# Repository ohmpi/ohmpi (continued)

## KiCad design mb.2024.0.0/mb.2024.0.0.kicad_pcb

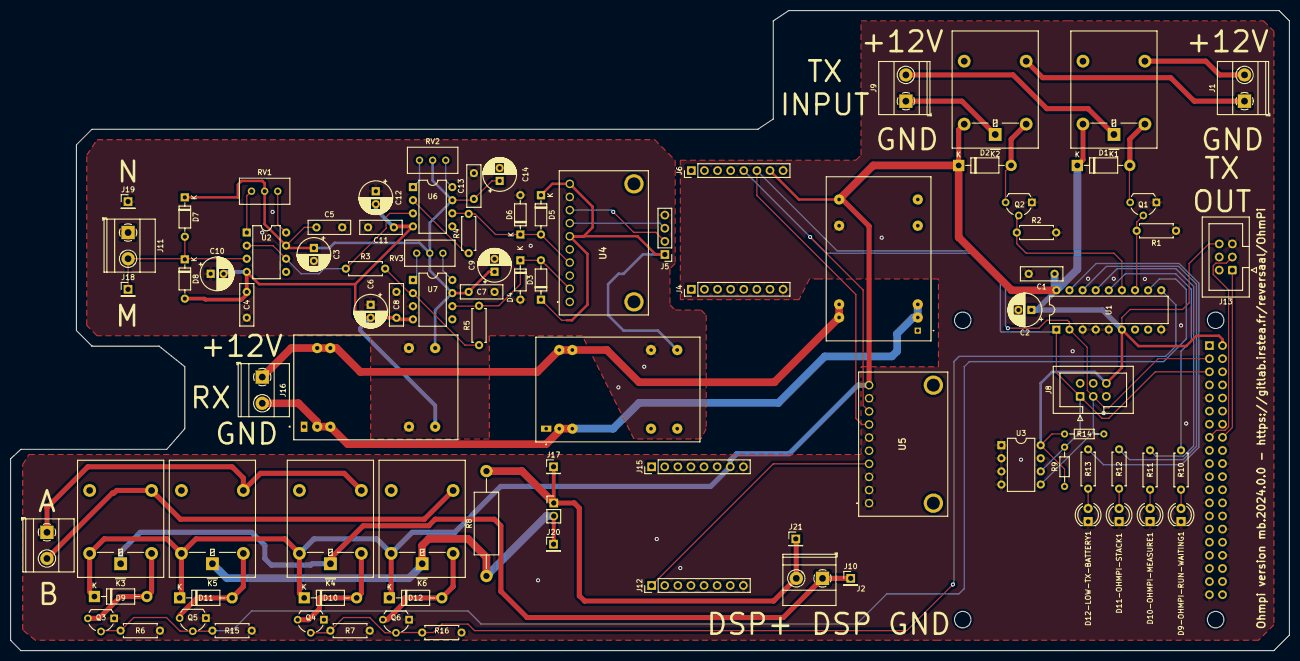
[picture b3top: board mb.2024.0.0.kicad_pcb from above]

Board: 2 copper layers, 247.8 x 124.0 mm, 92 parts (1 on the bottom side), 54 nets.

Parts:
Alim_5V_Digital_rasp_iso1540_mcp23008_current_7_click1, Alim_5V_I2C_isolator_Vmn_measurement1: THD_15-1211N; THD151211N
Alim_analog_Vmn_measurement_ina128P_lm158: THD_15-1222N; CONV_THD_15-1222N
C1, C4, C5, C7, C8, C11, C13: 100nF; C_Disc_D8.0mm_W2.5mm_P5.00mm
C2, C3, C6, C9, C10, C12, C14: 10uF; CP_Radial_D6.3mm_P2.50mm
D1, D2, D9, D10, D11, D12: 1N4001; D_DO-41_SOD81_P10.16mm_Horizontal
D3, D4, D5, D6, D7, D8: BAT86; D_DO-35_SOD27_P7.62mm_Horizontal
D9-OHMPI-RUN-WAITING1, D10-OHMPI-MEASURE1, D11-OHMPI-STACK1, D12-LOW-TX-BATTERY1: LED; LED_D4.0mm
J1: DSP_out_12v_GND; TerminalBlock_Phoenix_MKDS-1,5-2-5.08_1x02_P5.08mm_Horizont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
J2: DPS5005_input_0_to_50V; TerminalBlock_Phoenix_MKDS-1,5-2-5.08_1x02_P5.08mm_Horizont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
J3: Screw_Terminal_AB; TerminalBlock_Phoenix_MKDS-1,5-2-5.08_1x02_P5.08mm_Horizont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
J4, J6, J12, J15: Conn_01x08_Female; PinHeader_1x08_P2.54mm_Vertical
J5: Conn_01x04_Female; PinHeader_1x04_P2.54mm_Vertical
J7: Raspberry_Pi_2_3; PinSocket_2x20_P2.54mm_Vertical
J8: Connector_I2C_for_MCP23008; IDC-Header_2x03_P2.54mm_Vertical
J9: TX_bat; TerminalBlock_Phoenix_MKDS-1,5-2-5.08_1x02_P5.08mm_Horizont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
J10: DSP+; PinHeader_1x01_P2.54mm_Vertical
J11: Screw_Terminal_VMN; TerminalBlock_Phoenix_MKDS-1,5-2-5.08_1x02_P5.08mm_Horizont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
J13: Connector_I2C_for_mux; IDC-Header_2x03_P2.54mm_Vertical
J14: Conn_01x02_Female; PinHeader_1x02_P2.54mm_Vertical
J16: RX_bat; TerminalBlock_Phoenix_MKDS-1,5-2-5.08_1x02_P5.08mm_Horizont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
J17: DSP GND; PinHeader_1x01_P2.54mm_Vertical
J18: ELEC_M; PinHeader_1x01_P2.54mm_Vertical
J19: ELEC_N; PinHeader_1x01_P2.54mm_Vertical
J20: shunt +; PinHeader_1x01_P2.54mm_Vertical
J21: shunt -; PinHeader_1x01_P2.54mm_Vertical
K1, K2, K3, K4, K5, K6: G5LE-1; Relay_SPDT_Omron-G5LE-1
Q1, Q2, Q3, Q4, Q5, Q6: ZVN4206ASTZ; TO-92L_Wide
R1, R2, R6, R7, R15, R16: 100k; R_Axial_DIN0207_L6.3mm_D2.5mm_P7.62mm_Horizontal
R3, R4, R5: 1k; R_Axial_DIN0207_L6.3mm_D2.5mm_P7.62mm_Horizontal
R8: 2 ohms; R_Axial_DIN0414_L11.9mm_D4.5mm_P20.32mm_Horizontal
R9, R14: 4K7; R_Axial_DIN0204_L3.6mm_D1.6mm_P7.62mm_Horizontal
R10, R11, R12, R13: 330 ohms; R_Axial_DIN0207_L6.3mm_D2.5mm_P7.62mm_Horizontal
RV1, RV2, RV3: 10K; Potentiometer_Bourns_3296W_Vertical
U1: MCP23008-xP; DIP-18_W7.62mm
U2, U6, U7: OP07; DIP-8_W7.62mm
U3: 24LC02; DIP-8_W7.62mm
U4: 1115-Adress=0X49; 1085
U5: 1115-Adress=0X48; 1085

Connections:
5VA: Alim_5V_I2C_isolator_Vmn_measurement1.14 (+VOUT), D3.1 (K), D5.1 (K), J5.1, U4.6 (ADDR), U4.10 (VDD)
5VD: Alim_5V_Digital_rasp_iso1540_mcp23008_c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.14 (+VOUT), C1.1, C2.1, D1.1 (K), D2.1 (K), D9.1 (K), D10.1 (K), D11.1 (K), D12.1 (K), J6.7, J7.2 (5V), J8.6, J13.6, J15.7, K1.5, K2.5, K3.5, K4.5, K5.5, K6.5, R9.1, R14.1, U1.6 (~RESET), U1.18 (VDD), U3.8 (VCC), U5.10 (VDD)
+12V_A: Alim_analog_Vmn_measurement_ina128P_lm1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.14 (+VOUT), C3.1, C5.1, C7.1, C9.1, C13.1, C14.1, D7.1 (K), RV1.2, RV2.2, RV3.2, U2.7 (V+), U6.7 (V+), U7.7 (V+)
+12V_RX_bat: Alim_5V_Digital_rasp_iso1540_mcp23008_c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.22 (+VIN_(VCC)_1), Alim_5V_Digital_rasp_iso1540_mcp23008_c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.23 (+VIN_(VCC)_2), Alim_5V_I2C_isolator_Vmn_measurement1.22 (+VIN_(VCC)_1), Alim_5V_I2C_isolator_Vmn_measurement1.23 (+VIN_(VCC)_2), Alim_analog_Vmn_measurement_ina128P_lm1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.22 (+VIN(VCC)), Alim_analog_Vmn_measurement_ina128P_lm1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.23 (+VIN(VCC)), J16.1
+12V_TX_bat: J9.1, K2.1
-12V_A: Alim_analog_Vmn_measurement_ina128P_lm1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.11 (-VOUT), C4.1, C6.2, C8.1, C10.2, C11.1, C12.2, D8.2 (A), U2.4 (V-), U6.4 (V-), U7.4 (V-)
/Current_injection_and_measurement/A: J3.1, K4.3, K5.3
/Current_injection_and_measurement/B: J3.2, K3.3, K6.3
/Current_injection_and_measurement/Input_DSP_+_alim: J2.1, J10.1, K3.1, K4.1
/Current_injection_and_measurement/Input_DSP_GND_alim: J2.2, J14.1, J17.1, J21.1, R8.2
/Relay_switch_dsp/out_12v_DSP: J1.1, K2.3
/Relay_switch_dsp/out_GND_DSP: J1.2, K1.3
/Vmn_measurement/Electrode_M: D7.2 (A), D8.1 (K), J11.2, J18.1, U2.3 (+)
AN: J12.1, U5.4 (A0)
GNDA: Alim_5V_I2C_isolator_Vmn_measurement1.16 (-VOUT), Alim_analog_Vmn_measurement_ina128P_lm1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.9 (COMMON), Alim_analog_Vmn_measurement_ina128P_lm1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.16 (COMMON), C3.2, C4.2, C5.2, C6.1, C7.2, C8.2, C9.2, C10.1, C11.2, C12.1, C13.2, C14.2, D4.2 (A), D6.2 (A), J5.4, J11.1, J19.1, U4.9 (GND), U7.3 (+)
GNDD: Alim_5V_Digital_rasp_iso1540_mcp23008_c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.16 (-VOUT), C1.2, C2.2, D9-OHMPI-RUN-WAITING1.1 (K), D10-OHMPI-MEASURE1.1 (K), D11-OHMPI-STACK1.1 (K), D12-LOW-TX-BATTERY1.1 (K), J4.8, J6.8, J7.6 (GND), J7.9 (GND), J7.14 (GND), J7.20 (GND), J7.25 (GND), J7.30 (GND), J7.34 (GND), J7.39 (GND), J8.5, J12.8, J13.5, J15.8, Q1.1, Q2.1, Q3.1, Q4.1, Q5.1, Q6.1, R1.1, R2.2, R6.1, R7.1, R15.1, R16.1, U1.3 (A2), U1.4 (A1), U1.5 (A0), U1.9 (VSS), U3.1 (A0), U3.2 (A1), U3.3 (A2), U3.4 (GND), U3.7 (WP), U5.1 (A3), U5.2 (A2), U5.3 (A1), U5.6 (ADDR), U5.9 (GND)
GND_RX_bat: Alim_5V_Digital_rasp_iso1540_mcp23008_c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.2 (-VIN_(GND)_1), Alim_5V_Digital_rasp_iso1540_mcp23008_c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.3 (-VIN_(GND)_2), Alim_5V_I2C_isolator_Vmn_measurement1.2 (-VIN_(GND)_1), Alim_5V_I2C_isolator_Vmn_measurement1.3 (-VIN_(GND)_2), Alim_analog_Vmn_measurement_ina128P_lm1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.2 (-VIN(GND)), Alim_analog_Vmn_measurement_ina128P_lm1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.3 (-VIN(GND)), J16.2
GND_TX_bat: J9.2, K1.1
GP0: Q4.2, Q6.2, R7.2, R16.2, U1.10 (GP0)
GP1: Q3.2, Q5.2, R6.2, R15.2, U1.11 (GP1)
GP2: Q1.2, R1.2, U1.12 (GP2)
GP3: Q2.2, R2.1, U1.13 (GP3)
GP4: R10.1, U1.14 (GP4)
GP5: R11.1, U1.15 (GP5)
GP6: R12.1, U1.16 (GP6)
GP7: R13.1, U1.17 (GP7)
unnamed: D1.2 (A), K1.2, Q1.3
unnamed: D2.2 (A), K2.2, Q2.3
unnamed: D3.2 (A), D4.1 (K), R5.2, U4.2 (A2), U7.6
unnamed: D5.2 (A), D6.1 (K), R4.2, U4.4 (A0), U6.6
unnamed: D9-OHMPI-RUN-WAITING1.2 (A), R10.2
unnamed: D9.2 (A), K3.2, Q3.3
unnamed: D10-OHMPI-MEASURE1.2 (A), R11.2
unnamed: D10.2 (A), K4.2, Q4.3
unnamed: D11-OHMPI-STACK1.2 (A), R12.2
unnamed: D11.2 (A), K5.2, Q5.3
unnamed: D12-LOW-TX-BATTERY1.2 (A), R13.2
unnamed: D12.2 (A), K6.2, Q6.3
unnamed: J14.2, J20.1, K5.1, K6.1, R8.1
unnamed: R3.1, U2.2 (-), U2.6, U6.3 (+)
unnamed: R3.2, R5.1, U7.2 (-)
unnamed: R4.1, U6.2 (-)
unnamed: RV1.1, U2.8 (VOS)
unnamed: RV1.3, U2.1 (VOS)
unnamed: RV2.1, U6.8 (VOS)
unnamed: RV2.3, U6.1 (VOS)
unnamed: RV3.1, U7.8 (VOS)
unnamed: RV3.3, U7.1 (VOS)
SCL1: J6.5, J7.5 (SCL/GPIO3), J8.1, R9.2, U1.1 (SCL), U3.6 (SCL), U5.8 (SCL)
SCL2: J5.2, U4.8 (SCL)
SCL3: J7.16 (GPIO23), J13.1
SDA1: J6.6, J7.3 (SDA/GPIO2), J8.3, R14.2, U1.2 (SDA), U3.5 (SDA), U5.7 (SDA)
SDA2: J5.3, U4.7 (SDA)
SDA3: J7.15 (GPIO22), J13.3

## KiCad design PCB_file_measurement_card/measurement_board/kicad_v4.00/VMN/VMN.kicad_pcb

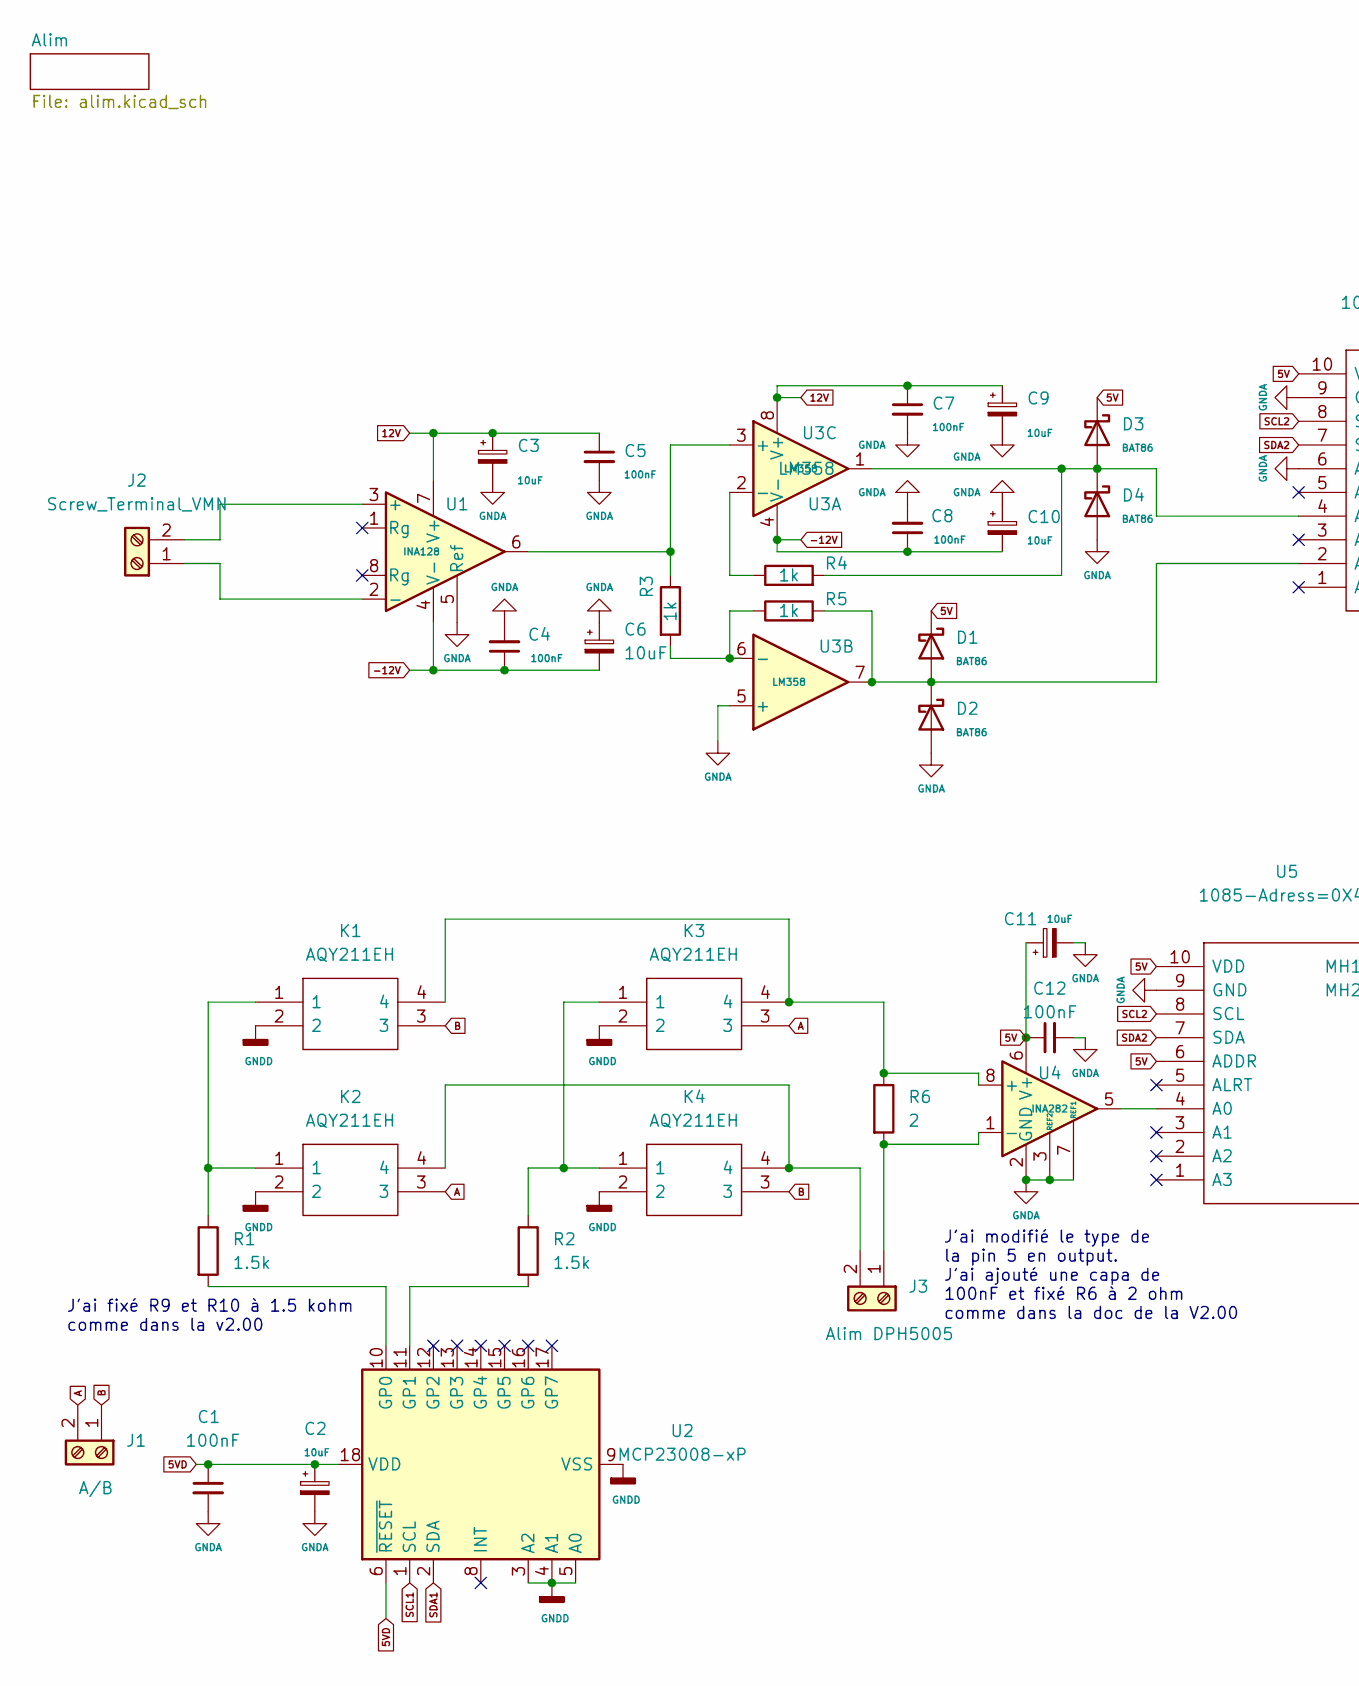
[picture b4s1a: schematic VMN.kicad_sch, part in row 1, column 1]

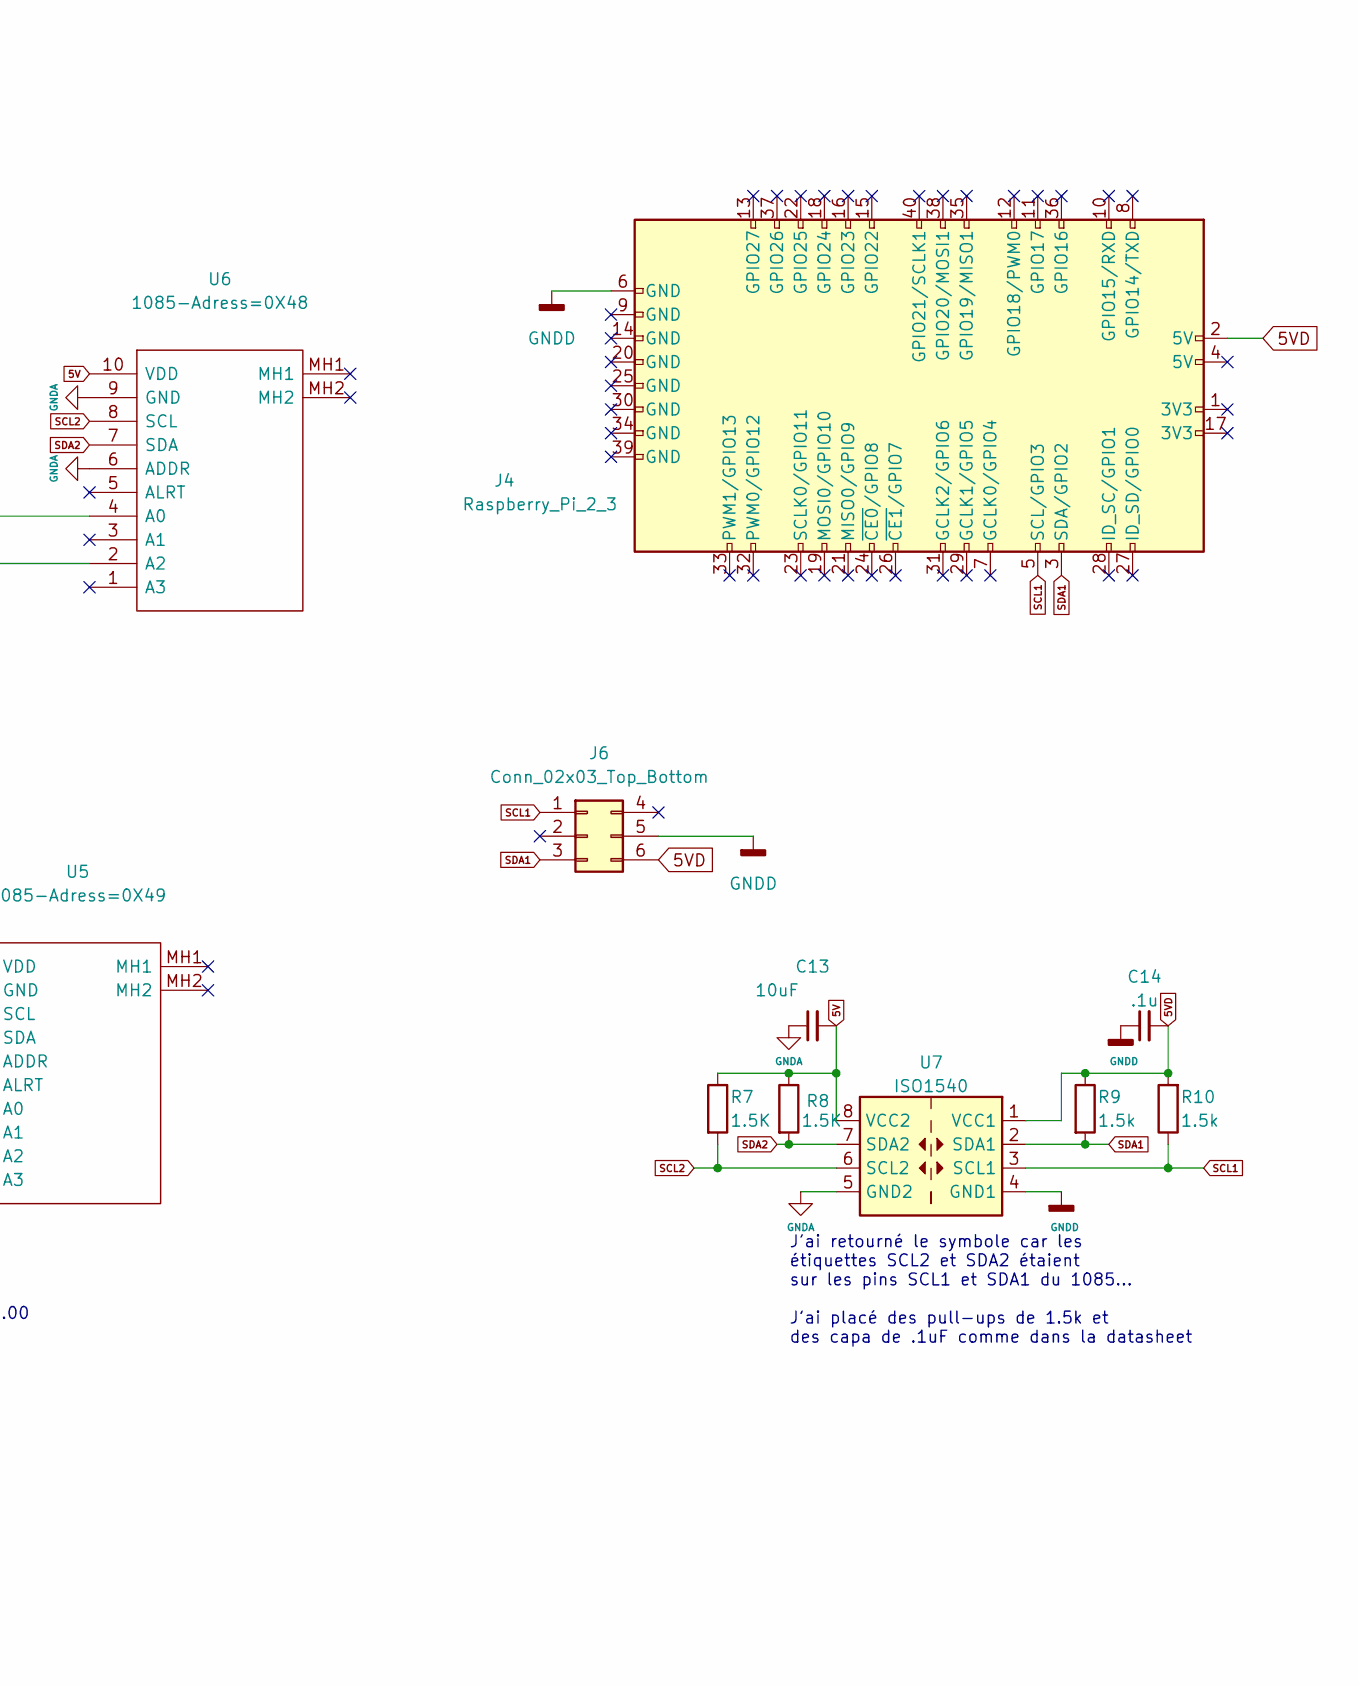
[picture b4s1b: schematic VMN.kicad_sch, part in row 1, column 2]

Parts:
C1, C4, C5, C7, C8, C12: 100nF; C_Disc_D8.0mm_W2.5mm_P5.00mm
C2, C3, C6, C9, C10, C11, C13: 10uF; CP_Radial_D6.3mm_P2.50mm
C14: .1u; C_Disc_D8.0mm_W2.5mm_P5.00mm
D1, D2, D3, D4: BAT86; D_DO-35_SOD27_P7.62mm_Horizontal
J1: A/B; TerminalBlock_Phoenix_MKDS-1,5-2-5.08_1x02_P5.08mm_Horizont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
J2: Screw_Terminal_VMN; TerminalBlock_Phoenix_MKDS-1,5-2-5.08_1x02_P5.08mm_Horizont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
J3: Alim DPH5005; TerminalBlock_Phoenix_MKDS-1,5-2-5.08_1x02_P5.08mm_Horizont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
J4: Raspberry_Pi_2_3; PinSocket_2x20_P2.54mm_Vertical
J6: Conn_02x03_Top_Bottom; IDC-Header_2x03_P2.54mm_Vertical
K1, K2, K3, K4: AQY211EH; DIP762W47P254L478H340Q4N; Manufacturer_Part_Number AQY211EH; Mouser Part Number 769-AQY211EH
R1, R2, R9, R10: 1.5k; R_Axial_DIN0207_L6.3mm_D2.5mm_P7.62mm_Horizontal
R3, R4, R5: 1k; R_Axial_DIN0207_L6.3mm_D2.5mm_P7.62mm_Horizontal
R6: 2; R_Axial_DIN0414_L11.9mm_D4.5mm_P20.32mm_Horizontal
R7, R8: 1.5K; R_Axial_DIN0207_L6.3mm_D2.5mm_P7.62mm_Horizontal
U1: INA128; DIP-8_W7.62mm
U2: MCP23008-xP; DIP-18_W7.62mm
U3: LM358; DIP-8_W7.62mm
U4: INA282; SOIC-8_3.9x4.9mm_P1.27mm
U5: 1085-Adress=0X49; 1085; PARTREV N/A; Mouser Part Number 485-1085
U6: 1085-Adress=0X48; 1085; PARTREV N/A; Mouser Part Number 485-1085
U7: ISO1540; SOIC-8_3.9x4.9mm_P1.27mm

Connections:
5V: C11.1, C12.1, C13.2, D1.1 (K), D3.1 (K), R7.1, R8.1, U4.6 (V+), U5.6 (ADDR), U5.10 (VDD), U6.10 (VDD), U7.8 (VCC2); also elsewhere on the board
5VD: C1.1, C2.1, C14.2, J4.2 (5V), J6.6, R9.1, R10.2, U2.6 (~RESET), U2.18 (VDD), U7.1 (VCC1); also elsewhere on the board
12V: C3.1, C5.1, C7.1, C9.1, U1.7 (V+), U3.8 (V+); also elsewhere on the board
-12V: C4.1, C6.2, C8.1, C10.2, U1.4 (V-), U3.4 (V-); also elsewhere on the board
A: J1.2, K2.3, K3.3
B: J1.1, K1.3, K4.3
GNDA: C1.2, C2.2, C3.2, C4.2, C5.2, C6.1, C7.2, C8.2, C9.2, C10.1, C11.2, C12.2, C13.1, D2.2 (A), D4.2 (A), U1.5 (Ref), U3.5 (+), U4.2 (GND), U4.3 (REF2), U4.7 (REF1), U5.9 (GND), U6.6 (ADDR), U6.9 (GND), U7.5 (GND2); also elsewhere on the board
GNDD: C14.1, J4.6 (GND), J6.5, K1.2, K2.2, K3.2, K4.2, U2.3 (A2), U2.4 (A1), U2.5 (A0), U2.9 (VSS), U7.4 (GND1); also elsewhere on the board
unnamed: D1.2 (A), D2.1 (K), R5.2, U3.7, U6.2 (A2)
unnamed: D3.2 (A), D4.1 (K), R4.2, U3.1, U6.4 (A0)
unnamed: J2.1, U1.2 (-)
unnamed: J2.2, U1.3 (+)
unnamed: J3.1, R6.2, U4.1 (-)
unnamed: J3.2, K2.4, K4.4
unnamed: K1.1, K2.1, R1.1
unnamed: K1.4, K3.4, R6.1, U4.8 (+)
unnamed: K3.1, K4.1, R2.1
unnamed: R1.2, U2.10 (GP0)
unnamed: R2.2, U2.11 (GP1)
unnamed: R3.1, U1.6, U3.3 (+)
unnamed: R3.2, R5.1, U3.6 (-)
unnamed: R4.1, U3.2 (-)
unnamed: U4.5, U5.4 (A0)
SCL1: J4.5 (SCL/GPIO3), J6.1, R10.1, U2.1 (SCL), U7.3 (SCL1)
SCL2: R7.2, U5.8 (SCL), U6.8 (SCL), U7.6 (SCL2)
SDA1: J4.3 (SDA/GPIO2), J6.3, R9.2, U2.2 (SDA), U7.2 (SDA1)
SDA2: R8.2, U5.7 (SDA), U6.7 (SDA), U7.7 (SDA2)

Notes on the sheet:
J'ai retourné le symbole car les étiquettes SCL2 et SDA2 étaient sur les pins SCL1 et SDA1 du 1085... J'ai placé des pull-ups de 1.5k et des capa de .1uF comme dans la datasheet
J'ai fixé R9 et R10 à 1.5 kohm comme dans la v2.00
J'ai modifié le type de la pin 5 en output. J'ai ajouté une capa de 100nF et fixé R6 à 2 ohm comme dans la doc de la V2.00

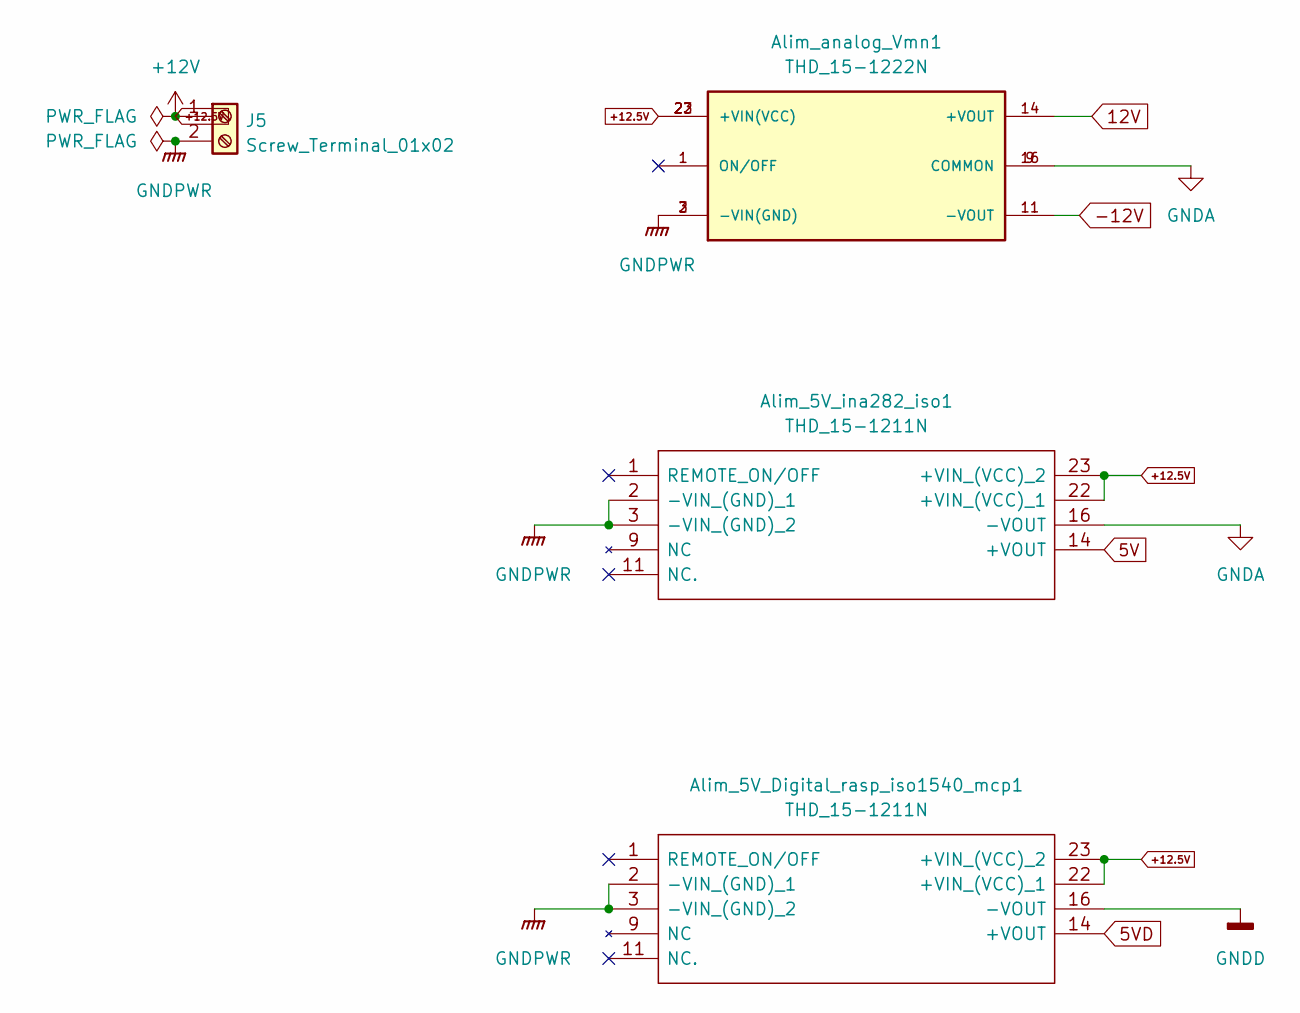
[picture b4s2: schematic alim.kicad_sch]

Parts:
Alim_5V_Digital_rasp_iso1540_mcp1, Alim_5V_ina282_iso1: THD_15-1211N; THD151211N; Manufacturer_Part_Number THD 15-1211N; Mouser Part Number 495-THD15-1211N
Alim_analog_Vmn1: THD_15-1222N; CONV_THD_15-1222N; PARTREV July 27, 2020
J5: Screw_Terminal_01x02; TerminalBlock_Phoenix_MKDS-1,5-2-5.08_1x02_P5.08mm_Horizont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

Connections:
5V: Alim_5V_ina282_iso1.14 (+VOUT); also elsewhere on the board
5VD: Alim_5V_Digital_rasp_iso1540_mcp1.14 (+VOUT); also elsewhere on the board
12V: Alim_analog_Vmn1.14 (+VOUT); also elsewhere on the board
+12.5V: Alim_5V_Digital_rasp_iso1540_mcp1.22 (+VIN_(VCC)_1), Alim_5V_Digital_rasp_iso1540_mcp1.23 (+VIN_(VCC)_2), Alim_5V_ina282_iso1.22 (+VIN_(VCC)_1), Alim_5V_ina282_iso1.23 (+VIN_(VCC)_2), Alim_analog_Vmn1.22 (+VIN(VCC)), Alim_analog_Vmn1.23 (+VIN(VCC)), J5.1
-12V: Alim_analog_Vmn1.11 (-VOUT); also elsewhere on the board
GNDA: Alim_5V_ina282_iso1.16 (-VOUT), Alim_analog_Vmn1.9 (COMMON), Alim_analog_Vmn1.16 (COMMON); also elsewhere on the board
GNDD: Alim_5V_Digital_rasp_iso1540_mcp1.16 (-VOUT); also elsewhere on the board
GNDPWR: Alim_5V_Digital_rasp_iso1540_mcp1.2 (-VIN_(GND)_1), Alim_5V_Digital_rasp_iso1540_mcp1.3 (-VIN_(GND)_2), Alim_5V_ina282_iso1.2 (-VIN_(GND)_1), Alim_5V_ina282_iso1.3 (-VIN_(GND)_2), Alim_analog_Vmn1.2 (-VIN(GND)), Alim_analog_Vmn1.3 (-VIN(GND)), J5.2

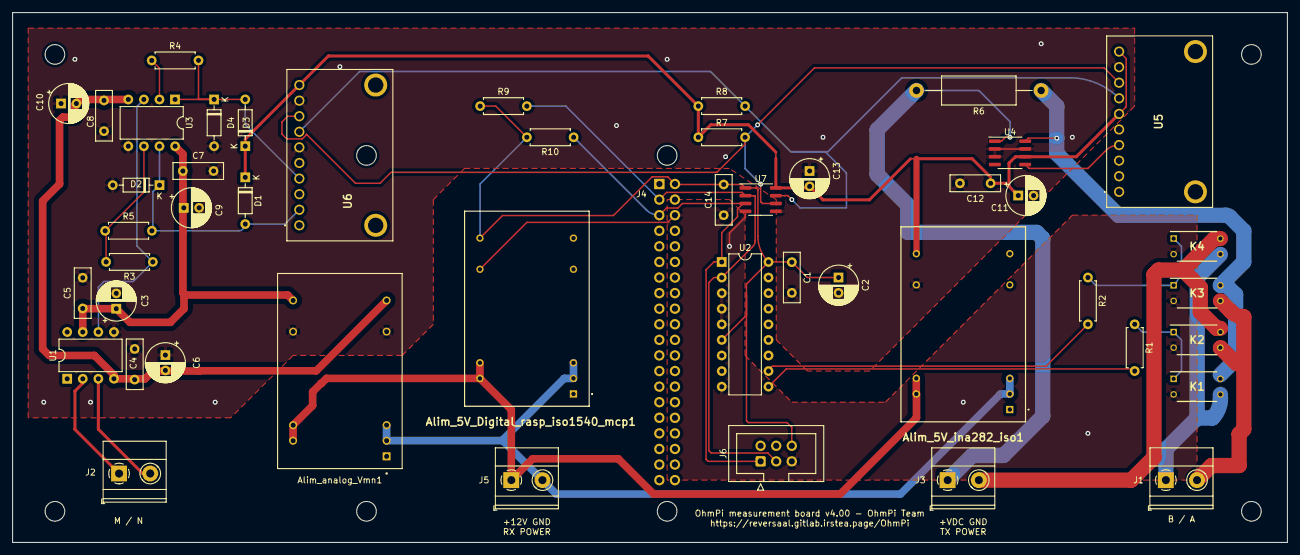
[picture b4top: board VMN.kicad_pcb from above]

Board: 2 copper layers, 207.8 x 86.4 mm, 48 parts (1 on the bottom side), 29 nets.

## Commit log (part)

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2024-06-28 Rename OhmPi to ohmpi in startup instructions for mqtt web interface
2024-06-28 #203 Uses the settings defined in config.py (was hardcoded before)
2024-06-30 Removes hex from soh_logger in MUX_2024_0_X init
2024-06-30 Adds colored text for soh_logger in MUX_2024_0_X init
2024-06-30 Adds colored text to identify mux board using soh_logger in MUX_2024_0_X init
2024-07-01 Adds minor changes to phmpi before merging v2024_0_bug_fix into 203_fix_issue
2024-07-01 Update BOM mux2024 and format
2024-07-01 Merges changes in pwr_dph5005
2024-07-01 fixes issue #212
2024-07-03 Use crontab to run web interface in user mode instead of rc.local, fix #195
2024-07-03 Fix #204
2024-07-03 v2024.0.15
2024-07-04 measurement board pads and track correction for THD
2024-07-04 update version number on the PCB
2024-07-04 Move sequence generator to sequence.py and refactor the code
2024-07-05 Fix typo in multigrad
2024-07-07 Import create_sequence()
2024-07-07 Add possible solution for #218 by asking the dph the UOUT in a breaking loop
2024-07-07 Update instruction for AP settings
2024-07-07 Update instruction ohmpiAP + fix bug data_web if data/ does not exists
2024-07-07 Add conversion from np.float64() to python float() when using numpy >= 2.0.0 This prevents logger reporting "Vmn": np.float64(3.22) instead of "Vmn": 3.22
2024-07-10 Fix typo
2024-07-10 Fix nonetype if no tca for mux2024
2024-07-10 v2024.0.16
2024-07-10 Fix issue with nonetype
2024-07-10 Update push_minor to fetch master before merging it (avoid conflicts)
2024-07-10 v2024.0.18
2024-07-10 Re-add back mux header on i2C test
2024-07-10 v2024.0.20
2024-07-10 If i2c_ext_tca not present, do not check for it
2024-07-10 v2024.0.22
2024-07-10 Web interface, don't overwrite log but append to it >> instead of >
2024-07-22 Modify figure to have width=100%, not fixed with, fix small doc typo
2024-07-22 Use figure instead of image within table (see #222)
2024-07-22 Improve for loop for setting DPH target voltage.
2024-07-22 Add config['pwr']['pwr_accuracy'] to control the for loop behavior of DPH5005
2024-07-22 Add quenched method (fix #133)
2024-07-22 v2024.0.25
2024-07-22 Polish OhmPi.create_sequence()
2024-07-22 Add joblib in requirements + fix fpath in OhmPi.create_sequence()
2024-07-23 Add OhmPi.set_time() in case RPI running in AP mode without internet
2024-07-23 Make joblib optional
2024-07-28 WIP accordion
2024-07-31 Add possibility to kill a multi-sequence acquisition during waiting time.
2024-08-07 Fix mux2024 pcb missing R10-gate ZVN connection
2024-08-07 Updates zone on MUX_2024.0.2 pcb
2024-08-10 Fix 'EVENT' error when setting up logger on new reinstantaion of OhmPi() WIP new UI, implement raw table
2024-08-11 Add log to webgui
2024-08-11 Add dpdp and wenner sequence
2024-08-11 Pass on sequence to sendCommand in saveConfigBtnFunc
2024-08-12 Add gradient and schlum array + download seq btn
2024-08-12 Add warning for soldering rpi header on under side of PCB + fix two -> three idc 6 pins
2024-08-13 Adding shortcut test for AB (working) and ABMN (not working great)
2024-08-13 WIP fixing webgui on the RPi
2024-08-19 Add ability to download files in a specified format in API
2024-08-19 Add invertedData retention + feedback inversion failed/success + fw avg info + download with specific ftype
2024-08-20 Update to user default mqtt_user and password (allow_anonymous=false)
2024-08-20 Update _test_mux_XX()
2024-08-20 Add everything ok
2024-08-20 Fix _test_mux_ABMN()
2024-08-20 Fix colored() and add np.median() for MN
2024-08-20 Fix swapped column in get_data()
2024-08-20 Update install.sh script for mqtt username/password default
2024-08-20 Fix traces quad when interrupted survey comes first
2024-08-20 Fix rscheck
2024-08-20 Update UI
2024-08-20 Update webgui
2024-08-20 Add V11 test (2.5V on A0 ADS voltage) to mb2025 checks
2024-08-21 v2024.0.26
2024-08-21 v2024.0.27
2024-09-18 Updates zone on MUX 2024 - no major change
2024-09-18 adds current_overload param and make it a setter getter to address #229
2024-09-18 fixes current_overload register to address #229
2024-09-18 Adds check to make current_overload not smaller than current_max #229
2024-09-23 Updates doc
2024-10-02 Update link to IDC socket and plug for mux2023
2024-10-07 Update relay mux2023 link with relay used in mux2024 (cheaper)
2024-10-07 Fix #232 (force countourpy version 1.0.1) as matplotlib dependency
2024-10-14 Fixes minor bug in mb_2024_1_X module
2024-10-19 Fixes bug documented in issue #236
2024-10-29 fix #237
2024-10-29 Update ohmpi.py export function
2024-10-30 Adds subclass management in rx init 2024_1_X
2024-10-30 Update dph_5005 specs
2024-10-30 Recompute pab_max
2024-10-30 v2024.0.28
2024-11-04 Remove os.chdir() from example
2024-11-04 WIP restructure
2024-11-04 Enforce numpy < 2.0.0 (fix float64 issues)
2024-11-04 Flatten software doc
2024-11-04 Add contributors section
2024-11-04 Reverts dph5005 voltage_max spec to 50.99V
2024-11-05 Adds a gain setting before each _find_vab
2024-11-05 Changes injection duration to 0.2s
2024-11-05 Add new directory
2024-11-05 Add new file
2024-11-05 Add hedges.rst
2024-11-05 add toctree
2024-11-05 Adds a message to debug
2024-11-05 Ajouter un nouveau répertoire
2024-11-05 Téléverser un nouveau fichier
2024-11-05 add pic hedges
2024-11-05 Update 2 files
    - /doc/source/source_rst/applications/hedges.rst
    - /doc/source/source_rst/gallery.rst
2024-11-05 add pic hedg
2024-11-05 Add slow ohmpi mqtt
2024-11-05 Changes iab_min
2024-11-05 Adds a debug message on iab_lower_bounds
2024-11-05 updates mux_2024_to_mux_2023
2024-11-05 Fix mapper in utils
2024-11-05 updates utils
2024-11-05 reset gain on tx before compute_vab
2024-11-05 fix reset gain on tx before compute_vab in mb_2023
2024-11-05 Set injection_duration in compute_vab
2024-11-05 Adds a short pulse of polarity 0 at the beginning of vab_square_wave
2024-11-05 Adds a short pulse of polarity 0 at the beginning of compute_vab
2024-11-05 ohmpi india first attempt at website
2024-11-05 Adapt example for 16 electrodes
2024-11-05 Update simple sequence example
2024-11-05 Fix dph5005 decay before setting vab in compute_vab
2024-11-05 Updates default.json and fixes small typos
2024-11-06 Reduce resolution size and remove old pictures
2024-11-06 add lab
2024-11-06 Remove unneeded pic
2024-11-06 Add map
2024-11-06 Update doc
2024-11-06 Update fig swale example
2024-11-06 Adds the interactive map module
2024-11-07 Add contributors
2024-11-07 Add marc
2024-11-07 coorection of example files
2024-11-07 Change pwr latency to 6s to be sure dph5005 is on
2024-11-07 v2024.0.33
2024-11-07 Remove source folder for doc
2024-11-07 Update ci with rules
2024-11-07 Small change
2024-11-07 Add map to system overview
2024-11-08 Update README.md with contributing section
2024-11-08 review how to contribute
2024-11-08 Add discord invitation link
2024-11-08 Add tips for a successfull ohmpi build
2024-11-08 Add pdf checklist for deployment
2024-11-08 Adding OhmPi.test() Tx.test() Rx.test()
2024-11-08 Add OhmPi.test_pwr()
2024-11-08 Fix tx.r_shunt() formula for deviation
2024-11-08 Add OhmPi.test() in troubleshooting
2024-11-08 Add CI test
2024-11-09 Improve coverage and add coverage.sh
2024-11-09 Add changelog
2024-11-09 Add posibility to write OhmPi.test(filename="test.json") to json (#259)
2024-11-09 Rename constant -> safe and full_constant -> fixed
2024-11-09 Add acquisition strategies in documentation
2024-11-10 Add documentation on pyramids of settings + graph of strategy (fix #211)
2024-11-10 Fix #196
2024-11-10 Implement injection_id
2024-11-10 Update UI with new headers and implement strategy
2024-11-10 Correct vmn_req unit from mV to V (also in webgui)
2024-11-10 Add calibration .py from hackathon 2024 (so we can remove calibration branch)
2024-11-11 Add new webgui pic + update description in doc + add video link
2024-11-11 Add hw_specs page
2024-11-11 Add 32bit os reason for slow ohmpi
2024-11-11 Add dg411 gain ratio (at rest! it works with mux) to OhmPi
2024-11-11 Fix #236
2024-11-11 Re-add pandas to requirements (for export, download, ...)
2024-11-11 Recommend restarting for reboot
2024-11-11 v2024.0.34
2024-11-11 Update bom list for mb2024
2024-11-13 Fixes typo and changes component link in MUX2024
2024-11-13 Adds link to boards in assemble systems
2024-11-14 Fix typo in troubleshooting
2024-11-26 Update pseudo-section screenshot webgui
2024-11-27 Tries to solve #267
2024-11-28 Fix doc bug with duplicated toctree in different pages (use links instead)
2024-11-28 Update to fix #267
2024-11-28 Add matplotlib to import
2024-11-29 Update mb2024 checks
2025-01-08 Add back gerber for mux2023.0.1 (fix #269)
2025-01-20 solves issue #271
2025-01-21 solves issue #271 by enlarging zones and removing via
2025-01-21 removing MUX.2024.0.2 #271
2025-01-22 adds new reference circuit #260
2025-01-29 Updates docs on MUX board v2024 after assembly
2025-01-29 Fixes I2C input on mux2024-text.jpg
2025-01-29 Fixes I2C input on mux2024-text.jpg and SCK in table
2025-02-05 adds error message when dph not connected via usb
2025-02-10 Updates doc on mux_2024
2025-02-11 Fix mb2024 test (no continuity with SDA/SCL from current click) + Add current debugging
2025-02-12 Add vmn voltage debugging instructions
2025-02-12 Add soldering to troubleshooting
2025-02-13 Restore __init__ line that dissapeared
2025-02-13 Fix dph5005 baudrate explanation
2025-02-13 Add warning for failed communication with power supply (inside ohmpihardware)
2025-02-13 Fix pseudo-section depth
2025-03-24 Add k.plot_last_fw() to troubleshooting
2025-03-28 updates checklist
2025-03-28 Add fw diagnostic to doc
2025-03-28 Add assembling of ohmpi lite 16
2025-03-28 Add ohmpi lite 16
2025-03-28 Add original pptx
2025-03-28 Fix number of mux
2025-03-28 updates strategy in example
2025-03-28 Enable shutdown, reboot and time set from user mode via os.system('sudo ...')
2025-03-28 Add 'sudo reboot' to reboot while in user mode
2025-03-29 Add mux bom list
2025-03-29 Supprimer ibom.html
2025-03-29 Update instructions for run_on_start
2025-03-29 Update bom in doc
2025-03-29 Add hardware error alert in webUI
2025-03-29 More general error mes
2025-03-29 Fixes issue 277
2025-03-29 v2024.0.35
2025-03-30 Typo specs 500 mA -> 50 mA
2025-03-30 updates doc ohmpi 16
2025-03-31 Update doc ok
2025-04-01 corrects manual check table for mux 2024
2025-04-01 Update order of mux2024 hardware check
2025-04-01 corrects manual check image for mux 2024
2025-04-01 Update doc mux2024-test
2025-04-01 Fix typo capa polarity step 15
2025-04-01 Add arrow step 15 on mb2024
2025-04-01 Update step15
2025-04-03 Add soh and ctrl to webgui
2025-04-03 Fix example from 'constant' to 'safe' in assembly doc
2025-04-03 Add numpy==1.26.4 to install_resipy.sh
2025-04-03 Update discord link
2025-04-03 Edit README.md
2025-04-03 Fix typo in geometric factor computation in UI
2025-04-04 Fix ohmpi_id read from config.py in webgui
2025-04-04 Fix #291
2025-04-06 Make more robust install.sh script
2025-04-07 removes sampling_interval references #202
2025-04-07 updates doc for mb2024
2025-04-07 updates doc for mux2024
2025-04-07 updates ohmpi map
2025-04-07 clarifies troubleshooting modbus
2025-04-07 clarifies troubleshooting intro
2025-04-07 Fix #289 and fix #282
2025-04-08 restructuring troubleshooting
2025-04-16 Update maps with latest registrations
2025-05-12 Fix typo + add discharge relay
2025-05-12 Add test mux2024 idc and screw
2025-08-25 Add .3f for electrodes
2025-08-26 Change fname_coord format to x,y,z csv with comma (like in ResIPy)
2025-09-08 Remove doc and add docs git submodule
2025-09-08 Update CI
2025-09-08 Use https for submodule url
2025-09-11 Add correct gerber for mb2024.1.1
2025-09-29 Fix #301
2025-10-01 Update docs commit
2026-01-12 Fixes version of library adafruit-circuitpython-ads1x15 in requirements.txt #311
2026-01-27 Refactors utcnow() due to deprecation
2026-06-15 Update docs
2026-06-15 Add compression DEFLATE to the zip for full-waveform
